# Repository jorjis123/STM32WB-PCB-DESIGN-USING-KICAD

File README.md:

**STM32 Bluetooth Development Board**

A compact, versatile development platform based on the STM32 architecture, designed for Bluetooth Low Energy (BLE) applications and rapid prototyping. This board integrates power management, USB connectivity, and RF capabilities in a small form factor.

**🚀 Key Features**

Microcontroller: Integrated STM32 MCU with Bluetooth support (QFN package).

Connectivity: * USB-C Port: For power and data communication.

UART Header (J4): Dedicated serial interface for debugging or external modules.

SWD Interface (J2): Tag-Connect or pogo-pin footprint for high-speed programming and debugging.

RF Design: * Onboard RF circuitry with an integrated filter (FLT1).

U.FL Connector (J1): For external antenna connection.

**User Interface:**

BOOT Button (SW1): Easy access to bootloader mode for firmware flashing.

Status LEDs for power and user-defined signals.

Power Management: Onboard LDO regulators (U2, U3) to manage USB power delivery.

**🛠 Hardware Overview**
Component Map
Reference	Description
U1	    STM32 Bluetooth MCU
USB	    USB Type-C Connector
J1	    RF U.FL Antenna Connector
J2	    SWD Programming Header (Footprint)
J4	    UART Communication Header
SW1	    Bootloader / User Switch
X1 / X2	High and Low-speed Crystal Oscillators

Programming:
The board can be programmed via the SWD (Serial Wire Debug) port using an ST-LINK/V2 or V3. To enter the built-in system bootloader for USB programming, hold the BOOT button while powering on or resetting the device.

**3D VIEW**

**PCB ROUTING**

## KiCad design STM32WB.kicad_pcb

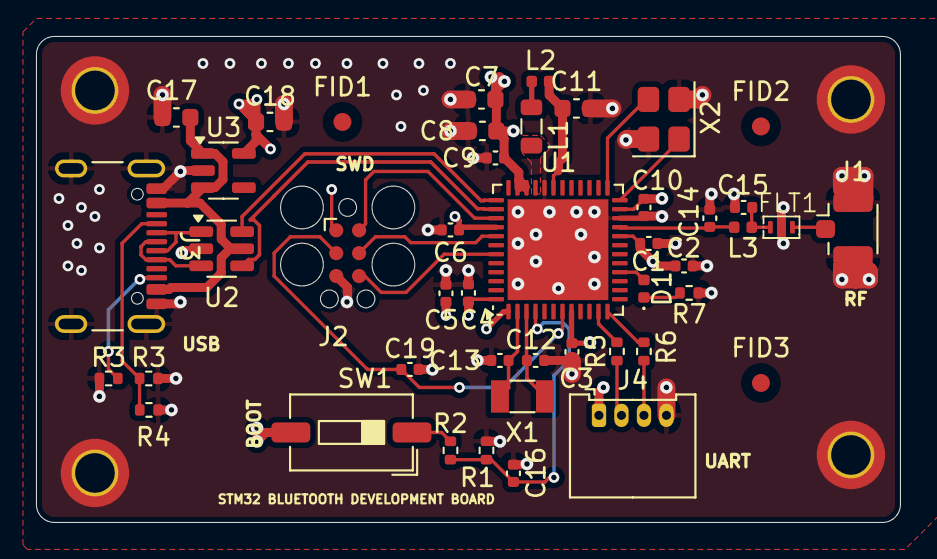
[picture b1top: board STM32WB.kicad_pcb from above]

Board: 4 copper layers, 48.0 x 27.0 mm, 49 parts (0 on the bottom side), 30 nets.

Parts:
C1, C2, C3, C4, C5, C6, C9, C10, C16, C19: 100n; C_0402_1005Metric
C7, C8, C11, C17, C18: 4u7; C_0603_1608Metric
C12, C13: 10p; C_0402_1005Metric
C14: 0p8; C_0402_1005Metric
C15: 0p3; C_0402_1005Metric
D1: LD274; LED_0402_1005Metric
FID1, FID2, FID3: Fiducial; Fiducial_1mm_Mask2mm
FLT1: DLF162500LT-5028A1
H1, H2, H3, H4: MountingHole_Pad; MountingHole_2.2mm_M2_ISO14580_Pad_TopOnly
J1: Conn_Coaxial; U.FL_Hirose_U.FL-R-SMT-1_Vertical
J2: TC2030; Tag-Connect_TC2030-IDC-FP_2x03_P1.27mm_Vertical
J3: USB_C_Receptacle_USB2.0_16P; USB_C_Receptacle_GCT_USB4105-xx-A_16P_TopMnt_Horizontal
J4: Conn_01x04_Pin; Molex_PicoBlade_53048-0410_1x04_P1.25mm_Horizontal
L1: 10n; L_0805_2012Metric
L2: 10u; L_0402_1005Metric
L3: 2n7; L_0402_1005Metric
R1, R3, R3#2, R4: 5k1; R_0402_1005Metric
R2, R5, R6, R7: 220R; R_0402_1005Metric
SW1: SW_Push; SW_DIP_SPSTx01_Slide_6.7x4.1mm_W6.73mm_P2.54mm_LowProfile_J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
U1: STM32WB55CCU6; QFN-48-1EP_7x7mm_P0.5mm_EP5.6x5.6mm
U2: USBLC6-2SC6; SOT-23-6
U3: MIC5365-3.3YD5; TSOT-23-5
X1: 32kHz768; Crystal_SMD_3215-2Pin_3.2x1.5mm
X2: 32MHz; Crystal_SMD_3225-4Pin_3.2x2.5mm

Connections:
+3V3: C1.1, C2.1, C3.1, C4.1, C5.1, C6.1, C7.1, C8.1, C9.1, C10.1, C18.1, J2.1 (VCC), J4.1, SW1.2, U1.1 (VBAT), U1.8 (VDDA), U1.20 (VDD), U1.23 (VDDRF), U1.34 (VDDSMPS), U1.35 (VDD), U1.40 (VDDUSB), U1.48 (VDD), U3.5 (VOUT)
+5V: C17.1, J3.A4 (VBUS), J3.A9 (VBUS), J3.B4 (VBUS), J3.B9 (VBUS), U2.5 (VBUS), U3.1 (VIN), U3.3 (EN)
/BOOT0: C16.1, R1.1, R2.1, U1.4 (PH3)
/LED_a: D1.2 (A), U1.16 (PA7)
/RF: C14.1, L3.1, U1.21 (RF1)
/RF_ANT: FLT1.3 (OUT), J1.1 (In)
/RF_MATCH: C15.1, FLT1.1 (IN), L3.2
/SMPS_FB: C11.1, L2.2, U1.31 (VFBSMPS)
/SMPS_LX: L1.1, U1.33 (VLXSMPS)
/SWD_CLK: J2.4 (SWCLK), U1.41 (PA14)
/SWD_DIO: J2.2 (SWDIO), U1.39 (PA13)
/SWD_NRST: C19.1, J2.3 (~RESET), U1.7 (NRST)
/SWD_TRC: J2.6 (SWO), U1.43 (PB3)
/UART_RX: R6.2, U1.12 (PA3)
/UART_RXC: J4.3, R6.1
/UART_TX: R5.2, U1.11 (PA2)
/UART_TXC: J4.2, R5.1
/USB_CC1: J3.A5 (CC1), R3.1, R4.1
/USB_CC2: J3.B5 (CC2), R3#2.2
/USB_D+: J3.A6 (D+), J3.B6 (D+), U1.38 (PA12), U2.3 (I/O2), U2.4 (I/O2)
/USB_D-: U1.37 (PA11), U2.6 (I/O1)
GND: C1.2, C2.2, C3.2, C4.2, C5.2, C6.2, C7.2, C8.2, C9.2, C10.2, C11.2, C12.2, C13.2, C14.2, C15.2, C16.2, C17.2, C18.2, C19.2, FLT1.2 (GND), FLT1.4 (GND), H1.1, H2.1, H3.1, H4.1, J1.2 (Ext), J2.5 (GND), J3.A1 (GND), J3.A12 (GND), J3.B1 (GND), J3.B12 (GND), J3.S1 (SHIELD), J4.4, R1.2, R3.2, R3#2.1, R4.2, R7.1, U1.22 (VSSRF), U1.32 (VSSSMPS), U1.49 (VSS), U2.2 (GND), U3.2 (GND), X2.2, X2.4
unnamed: D1.1 (K), R7.2
unnamed: J3.A7 (D-), J3.B7 (D-), U2.1 (I/O1)
unnamed: L1.2, L2.1
unnamed: R2.2, SW1.1
unnamed: U1.25 (OSC_IN), X2.3
unnamed: U1.24 (OSC_OUT), X2.1
unnamed: C13.1, U1.2 (PC14), X1.2
unnamed: C12.1, U1.3 (PC15), X1.1
